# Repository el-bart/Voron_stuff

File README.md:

# Voron stuff

my notes / mods / links for Voron 2.4 rev.2 350mm.
based on LDO kit (rev. C).

## docs
* [LDO docs](https://docs.ldomotors.com/en/voron/voron2)
* [LDO wiring guide for rev.C](https://docs.ldomotors.com/en/voron/voron2/wiring_guide_rev_c)

### installation
* [klipper firmware installation](https://docs.vorondesign.com/build/software/octopus_klipper.html)
  * STM32F446
  * 12MHz
  * USB interface
  * 32KiB bootloader offset
* [Voron startup checks](https://docs.vorondesign.com/build/startup/)

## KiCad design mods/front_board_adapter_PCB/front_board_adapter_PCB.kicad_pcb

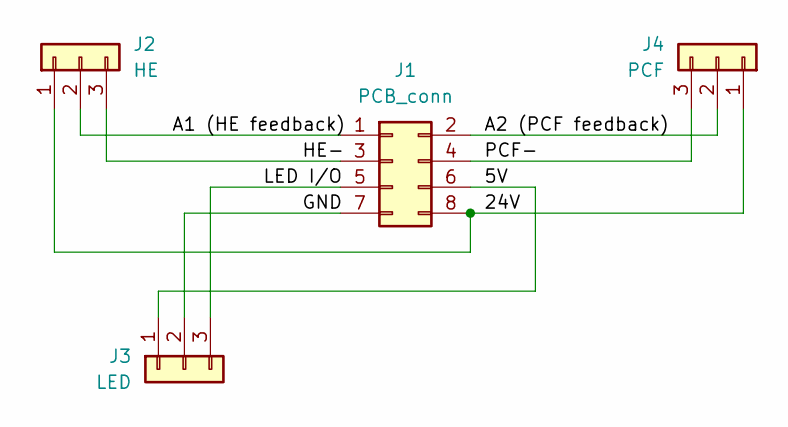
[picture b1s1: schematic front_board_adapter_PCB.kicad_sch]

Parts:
J1: PCB_conn; PinSocket_2x04_P2.54mm_Vertical
J2: HE; PinSocket_1x03_P2.00mm_Vertical
J3: LED; PinSocket_1x03_P2.00mm_Vertical
J4: PCF; PinSocket_1x03_P2.00mm_Vertical

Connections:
/5V: J1.6, J3.1
/24V: J1.8, J2.1, J4.1
/A1 (HE feedback): J1.1, J2.2
/A2 (PCF feedback): J1.2, J4.2
/GND: J1.7, J3.2
/HE-: J1.3, J2.3
/LED I/O: J1.5, J3.3
/PCF-: J1.4, J4.3

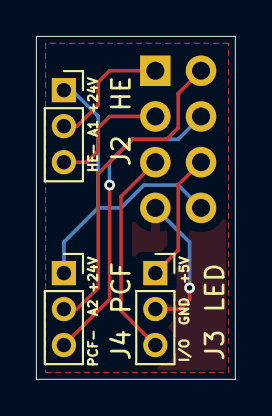
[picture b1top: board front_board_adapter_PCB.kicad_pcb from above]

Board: 2 copper layers, 11.0 x 19.1 mm, 4 parts (1 on the bottom side), 8 nets.

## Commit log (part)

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2024-07-18 ignore temp files
2024-07-18 touchscreem mount + link to the source
2024-07-18 adjusted print settings
2024-07-18 removed special characters from name, so that it can be copied to FAT32
2024-07-19 random info, before things get lost in time
2024-07-30 dev notes (misc)
2024-07-30 added disclamer
2024-07-30 renamed to signal it's mine printer
2024-07-30 LDO links and µC notes
2024-07-30 prep work for klipper.deb creation
2024-07-30 helper building script
2024-07-30 deb's control file
2024-07-30 draft of dockerfile for klipper
2024-07-31 moved config, logs and gcode to dedicated dirs
2024-07-31 log -> logs
2024-07-31 device and fs perms are now more fine-grained
2024-07-31 helper script to start docker compose
2024-07-31 using full option name
2024-07-31 added more features for klipper that will be needed by klipperscreen
2024-07-31 TODO for non-root running
2024-07-31 added more config options from moonraker's manual
2024-07-31 added missing links to klipper and other data dirs
2024-07-31 added X11 deps, for KlipperScreen
2024-07-31 TODO for nginx for WUI access
2024-07-31 example config for KlipperScreen
2024-07-31 placeholder for logs dir
2024-07-31 trying to setup x11kiosk - autostart X11 service
2024-07-31 klipperscreen build
2024-07-31 removed x11kiosk service (did not work)
2024-07-31 packaging all files as root
2024-07-31 udev touchscreen calibration
2024-07-31 added X11 screen config
2024-07-31 unclutter is not needed - klipperscreen handles that internally
2024-08-01 fixed path to connect moonraker to klipper
2024-08-01 temporary added X11 perms for root and basz
2024-08-01 * added inter-container deps * added local timezone handling * allowed power off / restart from container
2024-08-01 added helper service for starting klipper and stuff via docker-compose
2024-08-01 * fixed gcode include paths * fixed klipper's config path for moonraker * KlipperScreen is always restarting now
2024-08-01 KlipperScreen communicates with Moonraker over API key now; key is obtained from the DB at runtime
2024-08-01 added fluidd serving container + moved moonraker and klipperscreen back to docker's project network
2024-08-01 fixed warning about missing /opt/klipper/docs in moonraker
2024-08-01 added one more way to get API key
2024-08-01 comments and whitespaces
2024-08-01 nginx HTTP -> HTTPS redirection
2024-08-01 nginx added to docker-compose
2024-08-01 moved all configs into a subdir, for ease of mounting
2024-08-01 removed default_server reference
2024-08-01 disabled non-woirking include for proxy_params - likley not needed here anyway
2024-08-01 CORS definitions updated to match (new) reality
2024-08-01 nginx config is now simplified + fluidd runs interanlly only
2024-08-01 added websocket forwarding
2024-08-02 added more macros from https://docs.fluidd.xyz/configuration/initial_setup
2024-08-02 enabled exhaust fans, to auto-enable when heatbed goes to 60*C
2024-08-02 settings changed via WUI / LCD
2024-08-02 command to do things from the console
2024-08-02 PID calibration + saving + query endstops
2024-08-02 workaround to make sure serial console dir (docker moutn bind) is not gone when the only serial device is gone
2024-08-02 M114 + QUERY_PROBE
2024-08-02 bed probe status was inverted
2024-08-03 Revert "bed probe status was inverted" (actually the pin SHALL be inverter, to make sure thw switch works, before it's used!)
    This reverts commit 0bdf855f1f1a3aa3fb636d79efc3f972455c72d8.
2024-08-03 PROBE command + reorganization of calibration section
2024-08-03 z_offset calibration results
2024-08-03 probe calibration commands
2024-08-03 calibrated endstop phase for Z axis
2024-08-03 stock klicky probe's config with adjusted which cfg files are needed for Voron 2.4
2024-08-06 bed mesh config (not tested yet)
2024-08-06 including klicky probe config in kliuppers config
2024-08-06 moved LEDs ctrl to stealthburner config
2024-08-06 klicky probe docking and undocking is now woking
2024-08-06 horizontal_move_z must be more than z_offset
2024-08-06 re-calibrated z_offset with paper-test, after QGL and bed_mesh_calibrate
2024-08-07 link to docs on heating + temp adjusted
2024-08-07 heatbed PID tunning outcome
2024-08-07 hotend PID calibrated
2024-08-07 rotation_distance calibration results
2024-08-08 allow uploads up to 1GB
2024-08-08 gcodes/ is shared between klipper and moonraker
2024-08-08 z_offset re-cablibrated at bed at 60*C
2024-08-08 fixed endstpo position for OZ + z_offset recalibration
2024-08-08 using stealthburner color macros to indicate what's oging on at any given moment
2024-08-08 added macros for loading and unloading filament + increased max_extrude_only_distance to 10cm
2024-08-09 decreased controller fans speed, as it's not critical, yet VERY noisy
2024-08-10 not enabling extruder fans for PLA, as the case is opened there anyway
2024-08-11 LED status on pause / resume prints
2024-08-17 added comment on max heater power
2024-08-23 re-done bed mesh calibration
2024-08-26 PLA/precise
2024-08-26 aluminim profile mock
2024-08-26 holder -> mount
2024-08-26 moved to a printable position
2024-08-26 more perimiters, to make sure structure is sound (100% infill)
2024-08-26 better preview rendering of screw holes
2024-08-27 installed BTT SFS v2.0 filament runout & montion sensor
2024-08-31 adjusted BTT's SFS detection_length, to avoid false positives
2024-09-02 pause_on_runout: has to be 'true', to ensure it won't auto-resume (at a wrong height)
2024-09-02 adjusted pressure-advance, for better corner quality
2024-09-02 configured accelerometer to go through klipper_mcu (as it's supposed to)
2024-09-03 input shaper calibration results
2024-09-03 marked accelerometer type
2024-09-03 fixed formatting of individual items (bullet points)
2024-09-03 inpuit shaper: LDO docs + connection diagram
2024-09-03 LD kit is rev.C
2024-09-04 adjusted max_z_velocity, to sth that's actually possible
2024-09-04 * homing speed: 100 -> 300 mm/s * klicky probe docking speed: 50 -> 70 mm/s
2024-09-07 Orbiter 2.0 mount for SB
2024-09-07 3D SDK updated / fixed
2024-09-08 autoz default config
2024-09-08 added klipper_z_calibration plugin auto-installation
2024-09-08 autoz.cfg + some initial measurements
2024-09-08 added CALIBRATE_Z to the startup procedure
2024-09-08 moved separate elements to dir
2024-09-08 nicer name for the plate
2024-09-08 moved all elements to the main dir
2024-09-08 fixed position_endstop + position_min as needed
2024-09-16 max_velocity: 700 -> 600 (700mm/s may cause a missed steps on long runs)
2024-09-16 comment on 700mm/s
2024-09-17 helper BED_MESH_CALIBRATE
2024-09-17 bed mesh for LDO PEI 1B
2024-09-17 bed_mesh peo_pei_2b
2024-09-17 removed extra probing extension from z-probe
2024-09-17 bed mesh re-captured with more accurate version of klicky probe (w/o leaver)
2024-09-19 3D SDK for LED chassis light
2024-09-19 LED strip mock
2024-09-19 added LED support shelf (to glue them to)
2024-09-19 printing in Voron's PIF mode
2024-09-19 rotating in other direction, to have shorter runs on 1st layer
2024-09-19 adjusted LED angle, to make better ligthing
2024-09-20 added support disks at the edges
2024-09-20 added CALCULATE_SWITCH_OFFSET to docs
2024-09-20 added more links to docs
2024-09-26 re-homing is now conditional and only done when not homed yet + added nicer prints
2024-09-26 added PRIME_LINE macro, for priming extruder w/o skirts
2024-09-26 PRIME_LINE no longer retracts at the end, as it causes gaps at the beginning of the 1st layer
2024-09-28 model for IMX179-based camera module
2024-09-28 model from Printables
2024-09-28 ASA/none print
2024-09-28 ASA/voron_pif for camera holder
2024-09-28 plate with all elements for imx179
2024-09-29 moved to OpenSCAD to adjust all required sizes and orientations
2024-09-29 added extra logging on print start/end, pause/resume/cancel and load/unload filament
2024-09-29 * increased exhaust / filter fans from 0.5 to 0.66 * shortened prime line: 200mm -> 130mm * moved prime line to X=1 Y=1, for saving space
2024-10-01 3D SDK for aluminum profile cover
2024-10-01 aluminum profile cover element
2024-10-01 rounded corners
2024-10-01 second attempt, with a bit narrower internal slot
2024-10-02 adde CALIBRATE_Z_PROXY that's calling CALIBRATE_Z with additional prints + is available via macros menu on touchpad
2024-10-02 most action_respond_info() turned into RESPOND macros, to make sure things are shown at the right spots
2024-10-03 with new SDK (cooling=1) there's no need for most of the fan settings from previous iteration(s)
2024-10-05 ASA -> TPU/40D
2024-10-06 adjusted length to the final size
2024-10-06 USB cable cover belong to IMX179 camera mount
2024-10-06 no need for special settings for IMX cable cover anymore
2024-10-06 fluidd does not require websockets
2024-10-06 granted container access to the camera
2024-10-24 heating nozzle while it's on the side of the print
2024-10-27 fixed threaded inserts slots on camera holder
2024-10-27 3D SDK for nozzle wiper
2024-10-27 aluminium profile template
2024-10-27 added moutn groove and filament sledge
2024-10-27 added sponge hodler wall and screw hole
2024-10-27 fixed typo in profile name
2024-10-27 WIPE_NOZZLE added (see mods/nozzle_wiper/ for wiper box deisgn)
2024-10-27 at the end of the print, move nozzle over wipe-box (but still keep it high, not to crashi into a print)
2024-11-24 Revert "QGL at 5mm/s (not 10mm/s)"
    This reverts commit 5e5bde9afbc2c2d932c7b86a958d4453b7d820bc.
2025-02-12 helper assembly tool for linear rail lubrication
2025-02-12 helper script for generate gcode to jog print head around (e.g. for librication)
2025-02-12 added comment what this script does
2025-02-22 adjusted z-offset with (PROBE_CALIBRATE) and updated med mesh to be closer to the edges
2025-02-22 added [respond] section, to make notifications work
2025-02-22 removed z-calibration addon - no longer used
2025-02-22 commented out z-endstop-phase module
2025-03-10 removed klicky-probe macros and auto-z helper config
2025-03-10 KlipperScreen: v0.4.3 -> v0.4.5
2025-03-10 ensuring images are pulled and built on installation
2025-03-10 fluidd: v1.30.1 -> v1.32.6
2025-04-25 jogging around in planes to make the whole process faster (Z axis is the bottleneck)
2025-06-08 draft of mjpeg camera stream
2025-06-08 cornercam renamed and added to cert genreation + nginx RP
2025-06-08 whitespace thingy
2025-06-08 adjusted camera capture config to use current configuration
2025-06-08 configuration of user and password for cornercam is now fully-automatic
2025-06-09 * all containers except for nginx are read-only now * cornercam is now running with very low privileges
2025-06-09 using v1.0.0 of mjpeg_cam_stream_server
2025-06-13 mjpeg_stream_server bumped to v1.1.0
2025-06-15 do not rebuild images on each run
2025-07-05 added pre-heat cycle for both heatbed and hotend
2025-07-06 bed preheat is now optional - only if bed is too cold
2025-08-15 klipper bumped to v0.13.0
2025-08-15 more info about hotends
2025-08-15 M115 for firmware version added
2025-08-15 limited max_power of hotend to 50%, to avoid excessive power usage
2025-08-15 added extra safety-check for extruder's max_power, to avoid surprises
2025-08-15 PCF explained
2025-08-15 PID-recalibrated for Mosquito Magnum+ at 150°C
2025-08-15 70% hotend power
2025-08-15 PID for 250°C and 70% power
2025-08-17 fixed placeholder typo
2025-08-21 KiCad for fornt board adapter PCB
2025-08-21 back to KiCad 7.0
2025-08-21 fakeroot is failing for some reason
2025-08-21 Revert "fakeroot is failing for some reason"
    This reverts commit becfaa8016b4055da1aa0b6cfc2f7a926d45c595.
2025-08-21 KiCad 9.0
2025-08-21 adjusted position of LED connector's silkscreen
2025-08-23 3D SDK bump
2025-08-23 fan has to be on for this one to be printable
2025-08-23 combined cable cover + sensor holder
2025-08-30 adjusted pressure advance to height where 60mm box had 60mm outer diamter
2025-09-05 updated printer
2025-09-05 moved adaptor to a separate file, for a re-print
2025-09-05 re-ran input shaping for new extruder and hotend
2025-09-26 min temp set lower, to avoid false-positives
2025-10-11 G32 added
2025-11-24 * added chamber temp to titlebar * added ASA preheat
2026-01-18 mjpeg_server, klipper_mcu and kipperscreen moved to debian:13
2026-01-24 added generation of the audio sounds to the pacakge building step
2026-01-24 helper script for playing async sound
2026-01-24 fixed typo in audio text
2026-02-01 adjusted max-Z for jog-around g-code generator
2026-06-26 added comment on the source of new versions
